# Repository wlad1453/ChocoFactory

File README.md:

# ChocoFactory

In framework of this project a mechatronic packaging system is created. The mechanical part is build with Camozzi pneumatic drives and the electronic part with a   PLC on a microprocessor basis. The pneumatic drives are controlled vial pneumatic valves and MOSFET drives.
The feedback of the mechanism (positions of the elements) is given via digital magnetic Hall-efffect sensors.
The software is written on C++ and controls the whole cycle of the mechanism. Moreover for the goal of development the special part of the SW evaluats the entered by operator sycle phases (time points of each movement) and build the right mechanical movements sequence on its basis.

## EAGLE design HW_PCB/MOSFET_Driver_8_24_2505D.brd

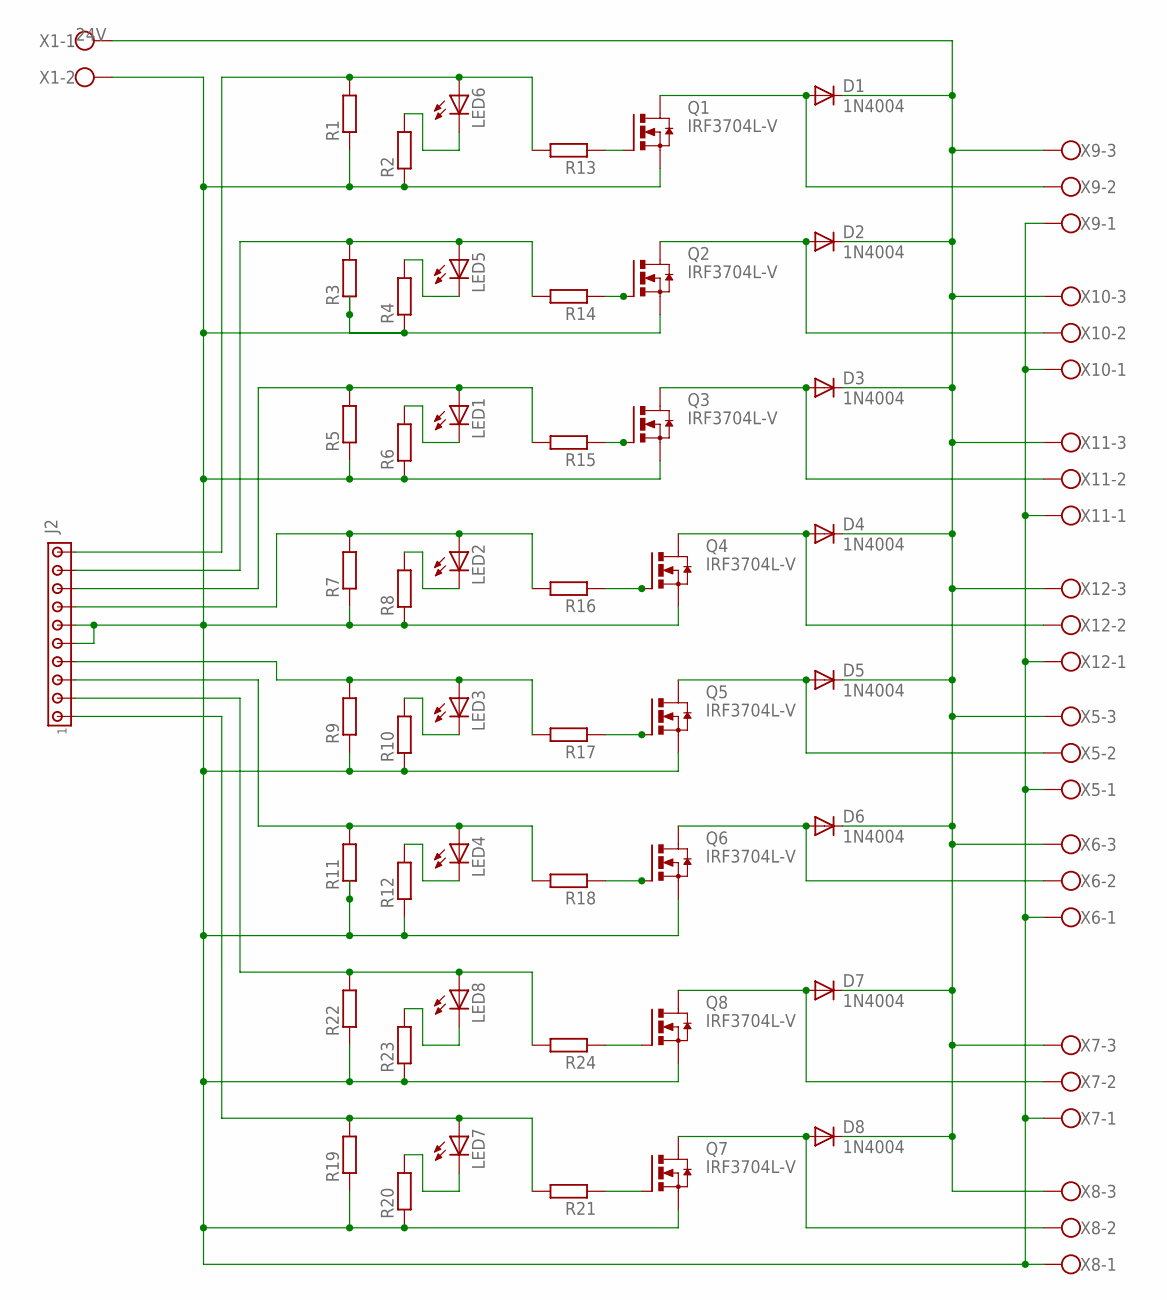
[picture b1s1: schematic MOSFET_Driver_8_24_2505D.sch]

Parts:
D1, D2, D3, D4, D5, D6, D7, D8: 1N4004; DO41-10
J2: MTA10-156; 1X10MTA
LED1, LED2, LED3, LED4, LED5, LED6, LED7, LED8: LED5MM
Q1, Q2, Q3, Q4, Q5, Q6, Q7, Q8: IRF3704L-V; TO262-V
R1, R2, R3, R4, R5, R6, R7, R8, R9, R10, R11, R12, R13, R14, R15, R16, R17, R18, R19, R20, R21, R22, R23, R24: R-EU_0207/10; 0207/10
X1: W237-102
X5, X6, X7, X8, X9, X10, X11, X12: W237-103

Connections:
unnamed: J2.10, LED6.A, R1.2, R13.2
unnamed: LED6.K (C), R2.2
unnamed: D1.A, Q1.2 (D), X9.2
unnamed: J2.1, LED7.A, R19.2, R21.2
unnamed: LED7.K (C), R20.2
unnamed: D3.A, Q3.2 (D), X11.2
unnamed: D2.A, Q2.2 (D), X10.2
unnamed: D4.A, Q4.2 (D), X12.2
unnamed: D5.A, Q5.2 (D), X5.2
unnamed: D6.A, Q6.2 (D), X6.2
unnamed: J2.9, LED5.A, R3.2, R14.2
unnamed: J2.8, LED1.A, R5.2, R15.2
unnamed: J2.7, LED2.A, R7.2, R16.2
unnamed: J2.4, LED3.A, R9.2, R17.2
unnamed: J2.3, LED4.A, R11.2, R18.2
unnamed: Q1.1 (G), R13.1
unnamed: Q2.1 (G), R14.1
unnamed: Q3.1 (G), R15.1
unnamed: LED5.K (C), R4.2
unnamed: LED1.K (C), R6.2
unnamed: LED2.K (C), R8.2
unnamed: LED3.K (C), R10.2
unnamed: LED4.K (C), R12.2
unnamed: Q4.1 (G), R16.1
unnamed: D1.C, D2.C, D3.C, D4.C, D5.C, D6.C, D7.C, D8.C, X1.1, X5.3, X6.3, X7.3, X8.3, X9.3, X10.3, X11.3, X12.3
unnamed: Q5.1 (G), R17.1
unnamed: Q6.1 (G), R18.1
unnamed: J2.5, J2.6, Q1.3 (S), Q2.3 (S), Q3.3 (S), Q4.3 (S), Q5.3 (S), Q6.3 (S), Q7.3 (S), Q8.3 (S), R1.1, R2.1, R3.1, R4.1, R5.1, R6.1, R7.1, R8.1, R9.1, R10.1, R11.1, R12.1, R19.1, R20.1, R22.1, R23.1, X1.2, X5.1, X6.1, X7.1, X8.1, X9.1, X10.1, X11.1, X12.1
unnamed: D8.A, Q7.2 (D), X8.2
unnamed: Q7.1 (G), R21.1
unnamed: J2.2, LED8.A, R22.2, R24.2
unnamed: LED8.K (C), R23.2
unnamed: D7.A, Q8.2 (D), X7.2
unnamed: Q8.1 (G), R24.1

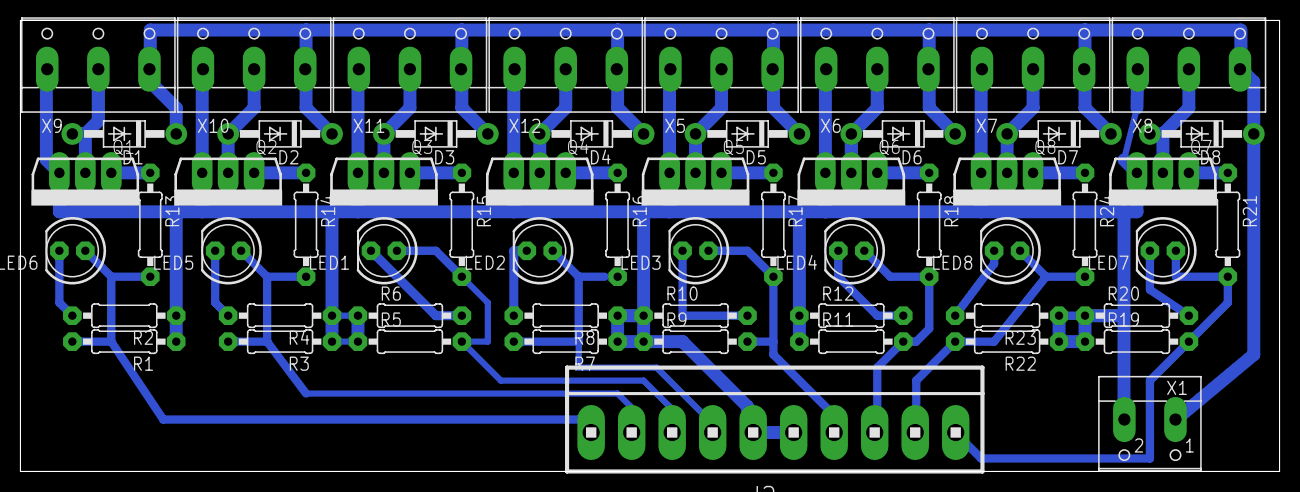
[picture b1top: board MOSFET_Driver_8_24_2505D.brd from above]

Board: 2 copper layers, 123.2 x 44.1 mm, 58 parts (0 on the bottom side), 34 nets.

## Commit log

2018-10-24 ReadMe.md
    This is a project of the automatization of a chocolate packing machine
2019-06-05 Add files via upload
    Assembled platform of pneumatical valves for the packing machine. All equipment used is Camozzi 3rd series valves with solenoid drives 24VDC. The pneumatical outlets are D4mm. The intake pipe is D6mm
2019-06-16 Create HW and PCBs
2020-11-22 Rename MOSFET_Driver_8_24_2505D.brd to HW_PCB/MOSFET_Driver_8_24_2505D.brd
2020-11-22 Rename MOSFET_Driver_8_24_2505D.sch to HW_PCB/MOSFET_Driver_8_24_2505D.sch
2020-11-27 Rename ChocoPack.txt to ChocoPack.md
